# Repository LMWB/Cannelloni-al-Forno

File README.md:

# Cannelloni-al-Forno
Timer Clock Arduino Shield and C-Library

# Description
I always wanted to use the world famous LD293D motor driver IC. Here I created a very simple application using this chip to build a timer clock that is able to drive some 12V loads.  
Since the LD293D is a THT device and the overall application i quite simple, I decided to build the hole board as THT as it was back in the days :) To give the board a little retro touch I gave the top and bottom layer a hole grid pcb design.  

# Real World Example
I used the [led constant current driver](https://github.com/LMWB/LED_CC_Driver?tab=readme-ov-file) to create a light for my courtyard.  

todo
- Xmas deciration
- composition of Canneloni-al-Forno and LED_CC_Driver

# Features
- 12V input (powers Nucleo board as well)
- 4 digital outputs (Vout = Vinput)
- RTC with coin cell back up battery

# todo
- add some sort of remote access (wifi, can, RS485,..)
- add shunt to track total energy consumption
- use TI DRV89xx instead of LD293D
- update noRTOS to latest version
- make timerclock multi instance to control different output channels

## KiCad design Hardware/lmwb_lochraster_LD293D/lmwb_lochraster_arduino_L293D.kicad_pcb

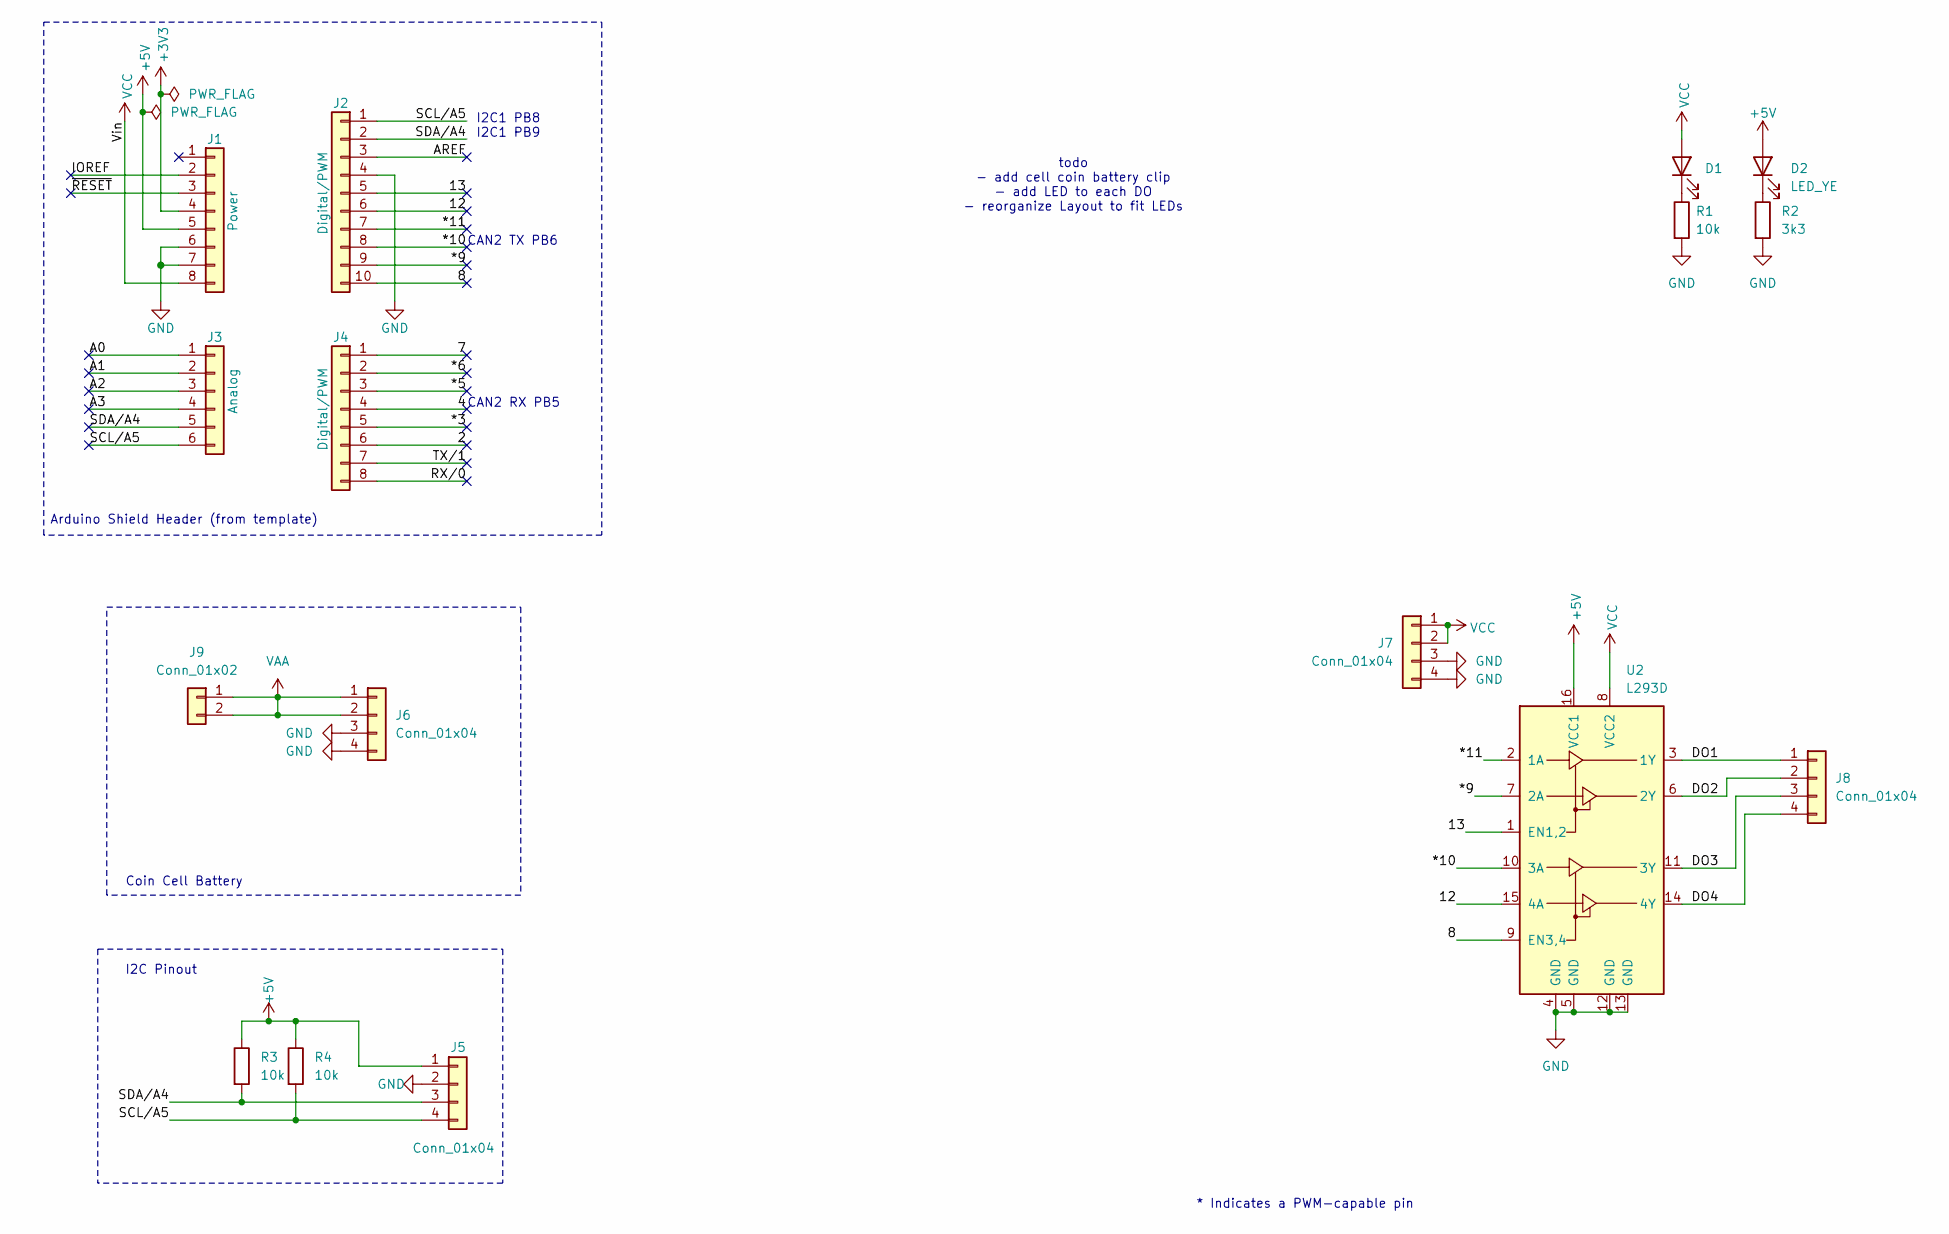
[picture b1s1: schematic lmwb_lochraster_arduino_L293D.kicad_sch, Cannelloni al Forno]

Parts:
D1, D2: LED_YE; LED_D3.0mm_Clear
J1: Power; PinSocket_1x08_P2.54mm_Vertical
J2: Digital/PWM; PinSocket_1x10_P2.54mm_Vertical
J3: Analog; PinSocket_1x06_P2.54mm_Vertical
J4: Digital/PWM; PinSocket_1x08_P2.54mm_Vertical
J5, J7, J8: Conn_01x04; PinHeader_1x04_P2.54mm_Vertical
J6: Conn_01x04; PinSocket_1x04_P2.54mm_Vertical
J9: Conn_01x02; PinHeader_1x02_P2.54mm_Vertical
R1, R3, R4: 10k; R_Axial_DIN0204_L3.6mm_D1.6mm_P5.08mm_Vertical
R2: 3k3; R_Axial_DIN0204_L3.6mm_D1.6mm_P5.08mm_Vertical
U2: L293D; DIP-16_W7.62mm

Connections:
+3V3: J1.4
+5V: D2.2 (A), J1.5, J5.1, R3.1, R4.1, U2.16 (VCC1)
/2: J4.6
/4: J4.4
/7: J4.1
/8: J2.10, U2.9 (EN3,4)
/12: J2.6, U2.15 (4A)
/13: J2.5, U2.1 (EN1,2)
/*3: J4.5
/*5: J4.3
/*6: J4.2
/*9: J2.9, U2.7 (2A)
/*10: J2.8, U2.10 (3A)
/*11: J2.7, U2.2 (1A)
/A0: J3.1
/A1: J3.2
/A2: J3.3
/A3: J3.4
/AREF: J2.3
/DO1: J8.1, U2.3 (1Y)
/DO2: J8.2, U2.6 (2Y)
/DO3: J8.3, U2.11 (3Y)
/DO4: J8.4, U2.14 (4Y)
/IOREF: J1.2
/RX/0: J4.8
/SCL/A5: J2.1, J3.6, J5.4, R4.2
/SDA/A4: J2.2, J3.5, J5.3, R3.2
/TX/1: J4.7
/~RESET: J1.3
GND: J1.6, J1.7, J2.4, J5.2, J6.3, J6.4, J7.3, J7.4, R1.2, R2.2, U2.4 (GND), U2.5 (GND), U2.12 (GND), U2.13 (GND)
unnamed: D1.1 (K), R1.1
unnamed: D2.1 (K), R2.1
VAA: J6.1, J6.2, J9.1, J9.2
VCC: D1.2 (A), J1.8, J7.1, J7.2, U2.8 (VCC2)

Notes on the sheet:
I2C1 PB8 I2C1 PB9
Coin Cell Battery
CAN2 RX PB5
todo - add cell coin battery clip - add LED to each DO - reorganize Layout to fit LEDs
CAN2 TX PB6
Arduino Shield Header (from template)
I2C Pinout
* Indicates a PWM-capable pin

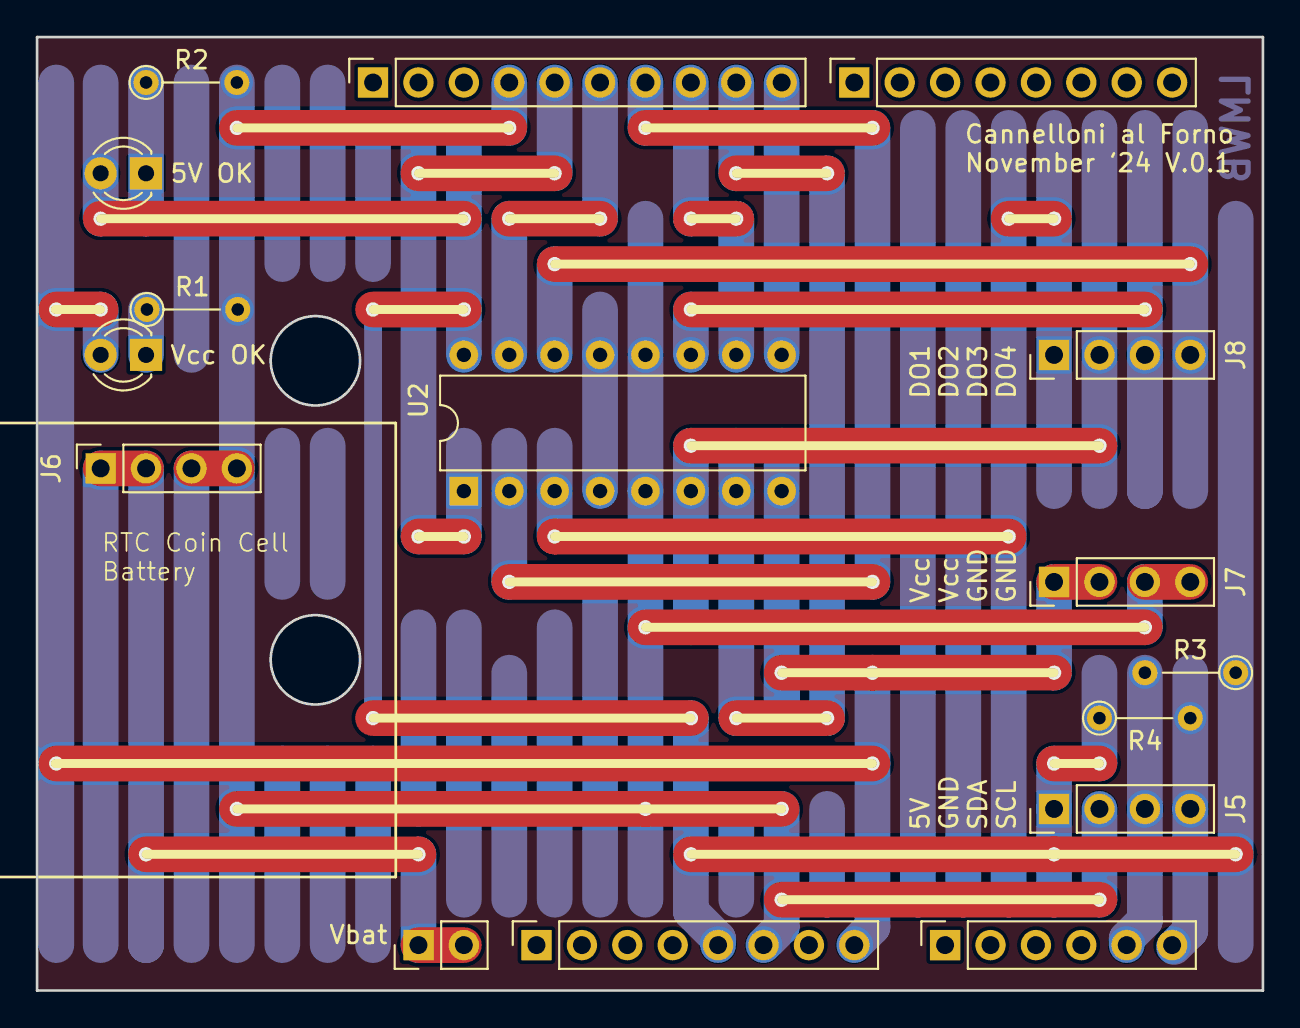
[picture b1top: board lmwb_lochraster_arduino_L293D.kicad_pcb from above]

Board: 2 copper layers, 68.6 x 53.3 mm, 16 parts (0 on the bottom side), 18 nets.

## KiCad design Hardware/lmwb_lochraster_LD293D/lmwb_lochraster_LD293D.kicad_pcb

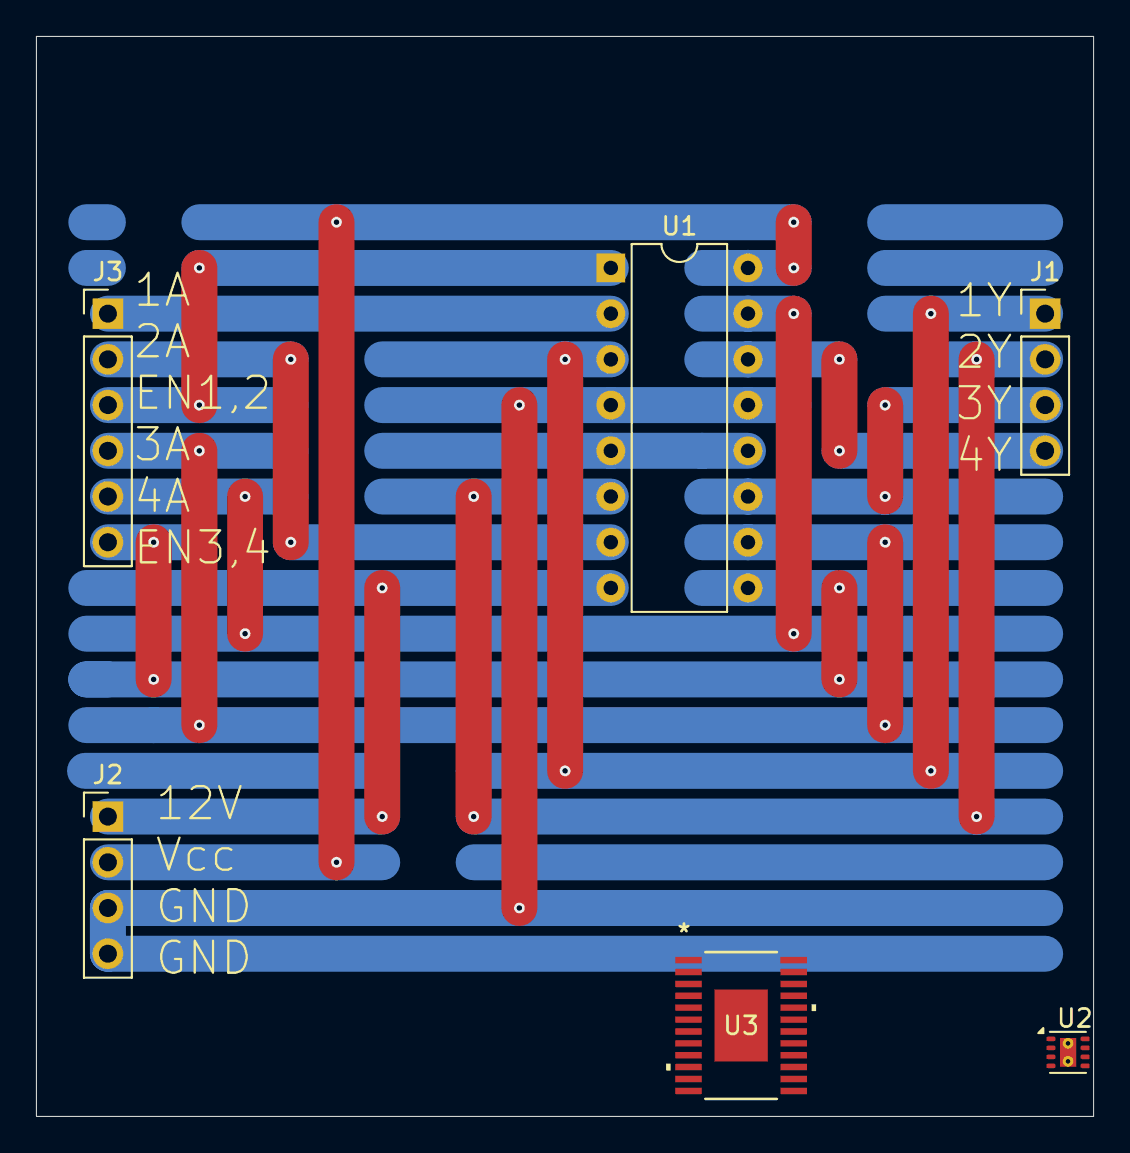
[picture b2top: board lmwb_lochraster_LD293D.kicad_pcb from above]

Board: 2 copper layers, 58.7 x 60.0 mm, 6 parts (0 on the bottom side), 13 nets.

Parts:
J1, J2: Conn_01x04; PinHeader_1x04_P2.54mm_Vertical
J3: Conn_01x06; PinHeader_1x06_P2.54mm_Vertical
U1: L293D; DIP-16_W7.62mm
U2: DRV8212P; WSON-8-1EP_2x2mm_P0.5mm_EP0.9x1.6mm_ThermalVias
U3: DRV8908QPWPRQ1; PWP24_4P5X7P9_TEX

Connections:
+VDC: J2.1, U1.8 (VCC2)
GND: J2.3, J2.4, U1.4 (GND), U1.5 (GND), U1.12 (GND), U1.13 (GND)
unnamed: J1.1, U1.3 (1Y)
unnamed: J1.2, U1.6 (2Y)
unnamed: J1.3, U1.11 (3Y)
unnamed: J1.4, U1.14 (4Y)
unnamed: J3.1, U1.2 (1A)
unnamed: J3.2, U1.7 (2A)
unnamed: J3.3, U1.1 (EN1,2)
unnamed: J3.4, U1.10 (3A)
unnamed: J3.5, U1.15 (4A)
unnamed: J3.6, U1.9 (EN3,4)
VCC: J2.2, U1.16 (VCC1)

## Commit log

2024-11-05 refectoring and clean up
2024-11-05 added project for STM32-L476
2024-11-05 make libs folder global to all projects
2024-11-05 include libs to STM32-L476 project
2024-11-09 changed uart2 to interrupt base without DMA
2024-11-12 preperation for AT Command tool set
2024-11-12 indroduced app.h/app.c moved all application code there
2024-11-18 update cubeMX .ioc file to match LD293 arduino shield
2024-11-18 update main.c (F446RE Part) to match LD293 arduino shield
2024-11-21 add hardware kicad files, minor changes in software/noRTOS
2024-11-22 added images and update readme
2024-11-23 README.md aktualisieren
2024-12-12 rename some timer utils
2024-12-12 setup new branch
2024-12-13 rtc works fine!
2025-11-30 return back to this branch after long time ago
2025-11-30 started PR to trace changes
2025-11-30 new RTC batt and fixed comments from PR
2025-12-01 minor consmetics, prep. merge
2025-12-01 started work on muli instance feature
2025-12-01 added release version info to boot sequence
2025-12-03 refactor API to work with pointer on instances
2026-02-19 added todo point
2026-02-19 added GPIO and code to load winter / summer profile
2026-03-23 testing summer light profile
2026-03-23 disable set_time in cube MX init()
2026-03-23 wrote a custom RTC_init() to prevent timer and date settings on reboot
